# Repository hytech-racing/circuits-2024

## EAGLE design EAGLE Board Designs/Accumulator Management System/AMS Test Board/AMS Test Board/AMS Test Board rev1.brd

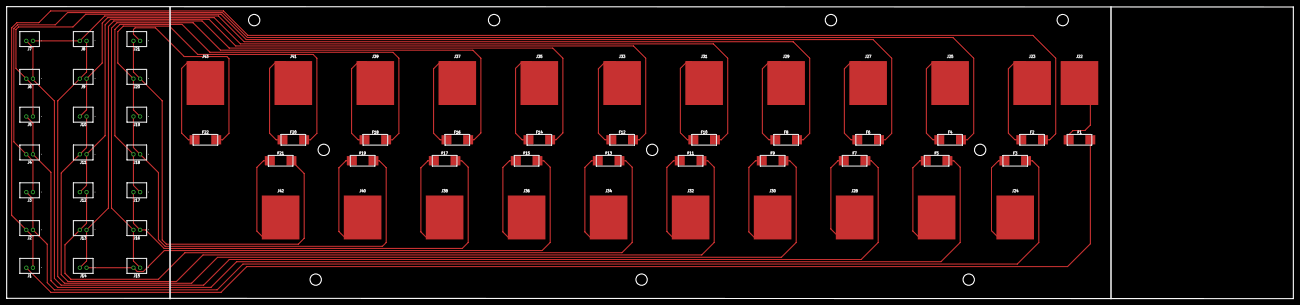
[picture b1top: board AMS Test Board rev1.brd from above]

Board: 2 copper layers, 386.6 x 87.7 mm, 75 parts (0 on the bottom side), 44 nets.

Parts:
F1, F2, F3, F4, F5, F6, F7, F8, F9, F10, F11, F12, F13, F14, F15, F16, F17, F18, F19, F20, F21, F22: FUSE_OMF_125_.5A; OMF_125
J1, J2, J3, J4, J5, J6, J7, J8, J9, J10, J11, J12, J13, J14, J15, J16, J17, J18, J19, J20, J21: CONNECTOR-2__B2B-PH-K; B2B-PH-K
J22, J23, J24, J25, J26, J27, J28, J29, J30, J31, J32, J33, J34, J35, J36, J37, J38, J39, J40, J41, J42, J43: CONNECTOR-1_5222; 5222
U$1, U$2, U$3, U$4, U$20, U$21, U$22, U$29, U$30, U$31: MOUNTING_M3

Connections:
1-: F1.2, J1.2
2-: F2.2, J1.1, J2.2
3-: F3.2, J2.1, J3.2
4-: F4.2, J3.1, J4.2
5-: F5.2, J4.1, J5.2
6-: F6.2, J5.1, J6.2
7-: F7.2, J6.1, J7.2
8-: F8.2, J7.1, J8.2
9-: F9.2, J8.1, J9.2
10-: F10.2, J9.1, J10.2
11-: F11.2, J10.1, J11.2
12-: F12.2, J11.1, J12.2
13-: F13.2, J12.1, J13.2
14-: F14.2, J13.1, J14.2
15-: F15.2, J14.1, J15.2
16-: F16.2, J15.1, J16.2
17-: F17.2, J16.1, J17.2
18-: F18.2, J17.1, J18.2
19-: F19.2, J18.1, J19.2
20-: F20.2, J19.1, J20.2
21+: F22.2, J21.1
21-: F21.2, J20.1, J21.2
unnamed: F1.1, J22.1
unnamed: F2.1, J23.1
unnamed: F3.1, J24.1
unnamed: F4.1, J25.1
unnamed: F5.1, J26.1
unnamed: F6.1, J27.1
unnamed: F7.1, J28.1
unnamed: F8.1, J29.1
unnamed: F9.1, J30.1
unnamed: F10.1, J31.1
unnamed: F11.1, J32.1
unnamed: F12.1, J33.1
unnamed: F13.1, J34.1
unnamed: F14.1, J35.1
unnamed: F15.1, J36.1
unnamed: F16.1, J37.1
unnamed: F17.1, J38.1
unnamed: F18.1, J39.1
unnamed: F19.1, J40.1
unnamed: F20.1, J41.1
unnamed: F21.1, J42.1
unnamed: F22.1, J43.1

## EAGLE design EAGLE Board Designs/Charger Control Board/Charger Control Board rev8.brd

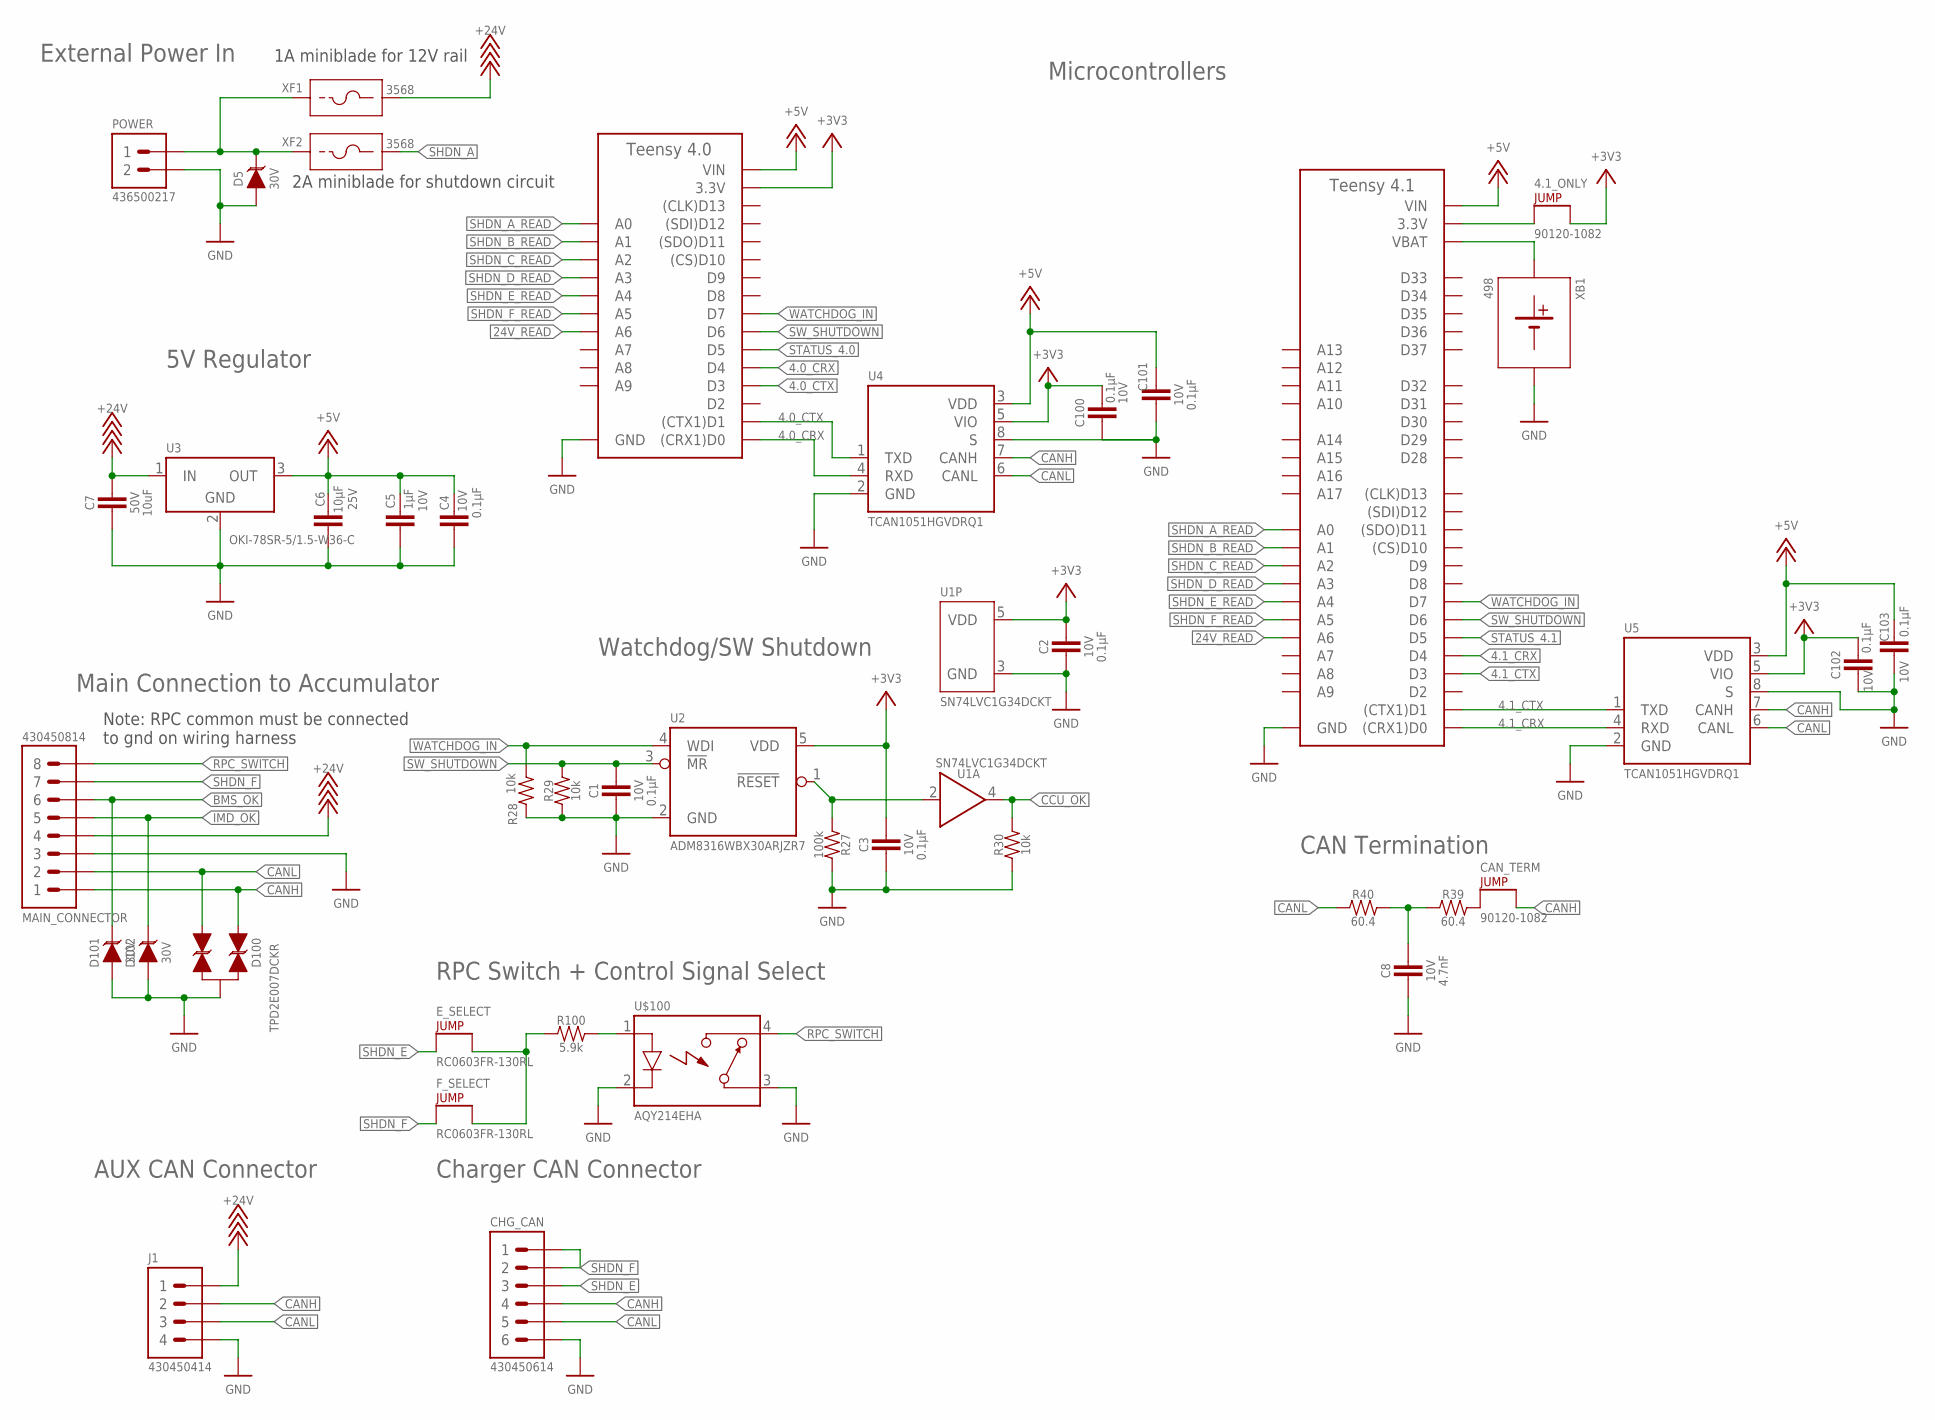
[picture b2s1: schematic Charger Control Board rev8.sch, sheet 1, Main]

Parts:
4.1_ONLY: JUMPER__1X02; 1X02
A1: TEENSY_4.1; TEENSY_LONG_EXT
A2: TEENSY_4.0TH; TEENSY_SHORT
C1, C2, C3, C4, C100, C101, C102, C103: CAPACITOR_0603_10V_0.1UF; 0603-CAP
C5: CAPACITOR_0603_10V_1UF; 0603-CAP
C6: CAPACITOR_0603_25V_10UF; 0603-CAP
C7: CAPACITOR_0805_50V_10UF; 0805-CAP
C8: CAPACITOR_0603_10V_4.7NF; 0603-CAP
CAN_TERM: JUMPER__1X02; 1X02
CHG_CAN: CONNECTOR-6_MF_T_V_; MOLEX_MICROFIT_PTH_VERTICAL_06_DUAL
D5, D101, D102: TVS_DO-214AA_30V; DO-214AA
D100: TVS_BIDIRECTIONAL_DUAL; SC-70-3
E_SELECT: JUMPER_0603_; 0603-RES
F_SELECT: JUMPER_0603_; 0603-RES
J1: CONNECTOR-4_μF_T_V_BLACK; MOLEX_MICROFIT_PTH_VERTICAL_04_DUAL
MAIN_CONNECTOR: CONNECTOR-8_MF_T_V_; MOLEX_MICROFIT_PTH_VERTICAL_08_DUAL
POWER: CONNECTOR-2_μF_T_V_; MOLEX_MICROFIT_PTH_VERTICAL_02_DUAL
R27: RESISTOR_0603_100K; 0603-RES
R28, R29, R30: RESISTOR_0603_10K; 0603-RES
R39, R40: RESISTOR_0603_60.4; 0603-RES
R100: RESISTOR_0603_5.9K; 0603-RES
U1: LOGICGATE_BUFFER; SC-70-5
U2: ADM8316WBX30; SOT-23-5
U3: VOLTAGE_REGULATOR_MODULE_OKI-78SR_5V; OKI-78SR
U4, U5: TCAN1051HQV-Q1; SOIC-08(NARROW,0.15")
U$100: RELAY_SOLIDSTATE_NO_DIP-4; DIP-4
XB1: BATTERY_HOLDER_KEYSTONE_498; 498
XF1, XF2: FUSE_HOLDER_MINIBLADEPTH; 3568

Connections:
4.0_CRX: A2.D0 ((CRX1)D0), A2.D4, U4.4 (RXD)
4.0_CTX: A2.D1 ((CTX1)D1), A2.D3, U4.1 (TXD)
4.1_CRX: A1.D0 ((CRX1)D0), A1.D4, U5.4 (RXD)
4.1_CTX: A1.D1 ((CTX1)D1), A1.D3, U5.1 (TXD)
24V_READ: A1.D20 (A6), A2.D20 (A6); also elsewhere on the board
+3V3: 4.1_ONLY.2, A2.3.3V, C2.2, C3.2, C100.2, C102.2, U1.5 (VDD), U2.5 (VDD), U4.5 (VIO), U5.5 (VIO); also elsewhere on the board
+5V: A1.VIN, A2.VIN, C4.2, C5.1, C6.1, C101.2, C103.2, U3.3 (OUT), U4.3 (VDD), U5.3 (VDD); also elsewhere on the board
+24V: C7.1, J1.1, MAIN_CONNECTOR.4, U3.1 (IN), XF1.3 (2), XF1.4 (2); also elsewhere on the board
BMS_OK: D101.2 (C), MAIN_CONNECTOR.6; also elsewhere on the board
CANH: CAN_TERM.2, CHG_CAN.4, D100.1 (C1), J1.2, MAIN_CONNECTOR.1, U4.7 (CANH), U5.7 (CANH)
CANL: CHG_CAN.5, D100.2 (C2), J1.3, MAIN_CONNECTOR.2, R40.1, U4.6 (CANL), U5.6 (CANL)
CCU_OK: R30.2, U1.4 (OUT); also elsewhere on the board
GND: A1.AGND/GND (GND), A1.GND, A1.GND@2 (GND), A2.AGND/GND (GND), A2.GND, C1.1, C2.1, C3.1, C4.1, C5.2, C6.2, C7.2, C8.2, C100.1, C101.1, C102.1, C103.1, CHG_CAN.6, D5.1 (A), D100.3 (A), D101.1 (A), D102.1 (A), J1.4, MAIN_CONNECTOR.3, POWER.2, R27.2, R28.2, R29.1, R30.1, U1.3 (GND), U2.2 (GND), U3.2 (GND), U4.2 (GND), U4.8 (S), U5.2 (GND), U5.8 (S), U$100.2 (CONTROL-), U$100.3 (CONTACT1), XB1.2 (MINUS); also elsewhere on the board
IMD_OK: D102.2 (C), MAIN_CONNECTOR.5; also elsewhere on the board
unnamed: D5.2 (C), POWER.1, XF1.1, XF1.2 (1), XF2.1, XF2.2 (1)
unnamed: R27.1, U1.2 (IN), U2.1 (!RESET!)
unnamed: CAN_TERM.1, R39.2
unnamed: E_SELECT.2, F_SELECT.2, R100.1
unnamed: A1.VBAT, XB1.1 (PLUS)
unnamed: C8.1, R39.1, R40.2
unnamed: R100.2, U$100.1 (CONTROL+)
unnamed: 4.1_ONLY.1, A1.3V3 (3.3V), A1.3V3@2 (3.3V), A1.3V3@3 (3.3V)
RPC_SWITCH: MAIN_CONNECTOR.8, U$100.4 (CONTACT2)
SHDN_A: XF2.3 (2), XF2.4 (2); also elsewhere on the board
SHDN_A_READ: A1.D14 (A0), A2.D14 (A0); also elsewhere on the board
SHDN_B_READ: A1.D15 (A1), A2.D15 (A1); also elsewhere on the board
SHDN_C_READ: A1.D16 (A2), A2.D16 (A2); also elsewhere on the board
SHDN_D_READ: A1.D17 (A3), A2.D17 (A3); also elsewhere on the board
SHDN_E: CHG_CAN.3, E_SELECT.1; also elsewhere on the board
SHDN_E_READ: A1.D18 (A4), A2.D18 (A4); also elsewhere on the board
SHDN_F: CHG_CAN.1, CHG_CAN.2, F_SELECT.1, MAIN_CONNECTOR.7; also elsewhere on the board
SHDN_F_READ: A1.D19 (A5), A2.D19 (A5); also elsewhere on the board
STATUS_4.0: A2.D5; also elsewhere on the board
STATUS_4.1: A1.D5; also elsewhere on the board
SW_SHUTDOWN: A1.D6, A2.D6, C1.2, R29.2, U2.3 (!MR!)
WATCHDOG_IN: A1.D7, A2.D7, R28.1, U2.4 (WDI)

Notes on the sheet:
External Power In
5V Regulator
Main Connection to Accumulator
CAN Termination
Microcontrollers
Watchdog/SW Shutdown
Charger CAN Connector
AUX CAN Connector
1A miniblade for 12V rail
2A miniblade for shutdown circuit
RPC Switch + Control Signal Select
Note: RPC common must be connected to gnd on wiring harness

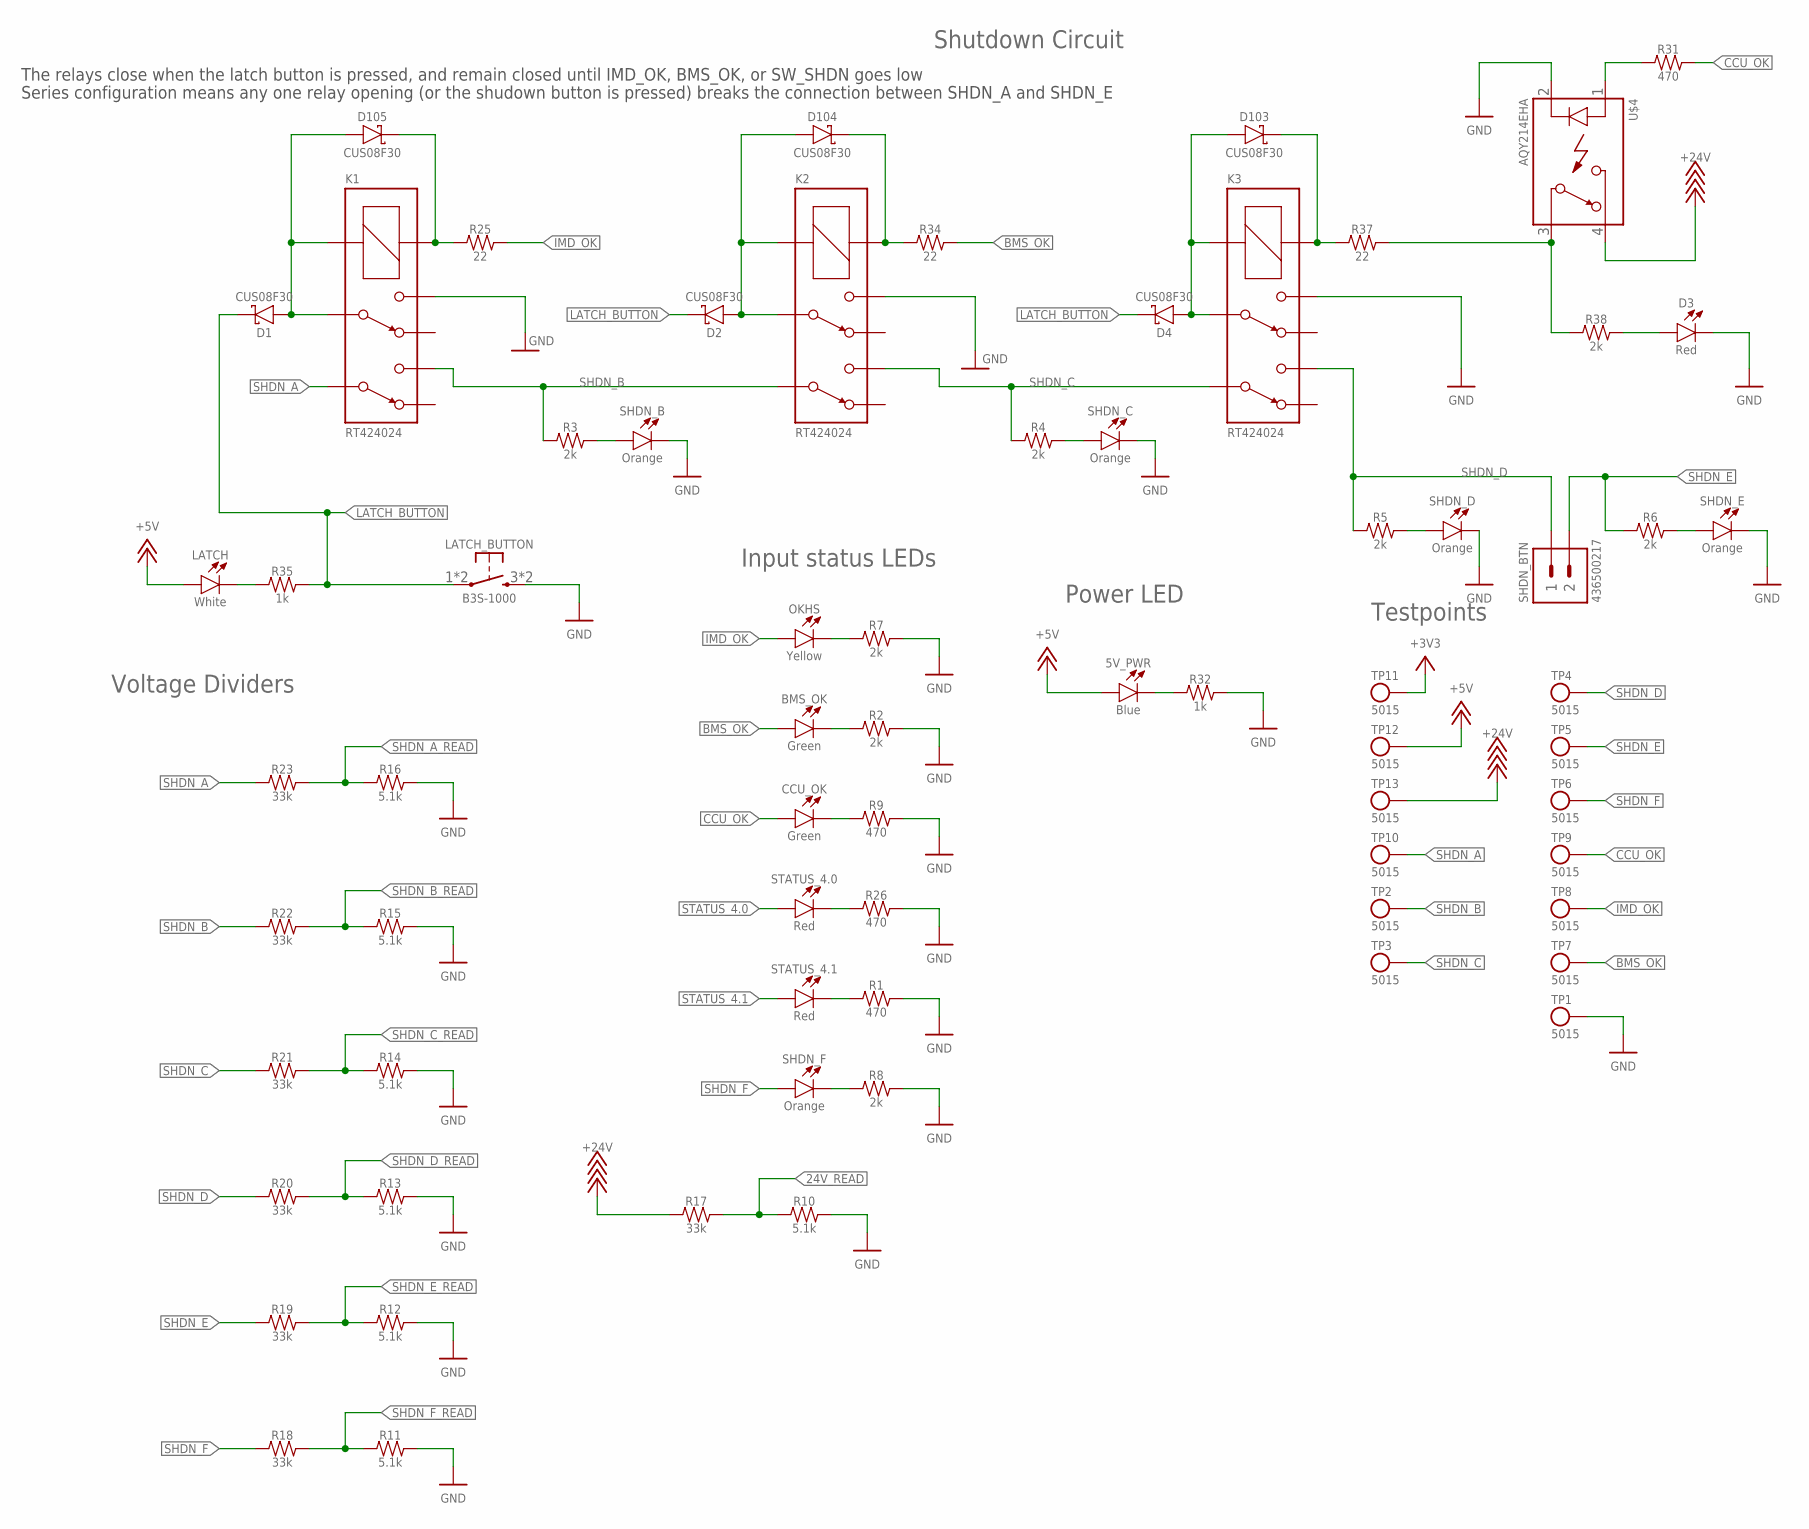
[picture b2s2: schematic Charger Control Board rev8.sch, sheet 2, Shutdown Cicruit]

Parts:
5V_PWR: LED_0603_BLUE; 0603-LED
BMS_OK: LED_0603_GREEN; 0603-LED
CCU_OK: LED_0603_GREEN; 0603-LED
D1, D2, D4, D103, D104, D105: SCHOTTKY_SOD323_30V; SOD-323
D3: LED_0603_RED; 0603-LED
K1, K2, K3: RELAY_DPDT_RT424024TH; RT*2*
LATCH: LED_0603_WHITE; 0603-LED
LATCH_BUTTON: BUTTON; B3S-100X
OKHS: LED_0603_YELLOW; 0603-LED
R1, R9, R26, R31: RESISTOR_0603_470; 0603-RES
R2, R3, R4, R5, R6, R7, R8, R38: RESISTOR_0603_2K; 0603-RES
R10, R11, R12, R13, R14, R15, R16: RESISTOR_0603_5.1K; 0603-RES
R17, R18, R19, R20, R21, R22, R23: RESISTOR_0603_33K; 0603-RES
R25, R34, R37: RESISTOR_0603_22; 0603-RES
R32, R35: RESISTOR_0603_1K; 0603-RES
SHDN_B: LED_0603_ORANGE; 0603-LED
SHDN_BTN: CONNECTOR-2_μF_T_V_; MOLEX_MICROFIT_PTH_VERTICAL_02_DUAL
SHDN_C: LED_0603_ORANGE; 0603-LED
SHDN_D: LED_0603_ORANGE; 0603-LED
SHDN_E: LED_0603_ORANGE; 0603-LED
SHDN_F: LED_0603_ORANGE; 0603-LED
STATUS_4.0, STATUS_4.1: LED_0603_RED; 0603-LED
TP1, TP2, TP3, TP4, TP5, TP6, TP7, TP8, TP9, TP10, TP11, TP12, TP13: TEST_POINT; 5015
U$4: RELAY_SOLIDSTATE_NO; DIP-4@1

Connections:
24V_READ: R10.1, R17.2; also elsewhere on the board
+3V3: TP11.1; also elsewhere on the board
+5V: 5V_PWR.2 (A), LATCH.2 (A), TP12.1; also elsewhere on the board
+24V: R17.1, TP13.1, U$4.4 (CONTACT2); also elsewhere on the board
BMS_OK: BMS_OK.2 (A), R34.2, TP7.1; also elsewhere on the board
CCU_OK: CCU_OK.2 (A), R31.2, TP9.1; also elsewhere on the board
GND: D3.1 (C), K1.14 (4), K2.14 (4), K3.14 (4), LATCH_BUTTON.3 (S), LATCH_BUTTON.4 (S), R1.2, R2.2, R7.2, R8.2, R9.2, R10.2, R11.2, R12.2, R13.2, R14.2, R15.2, R16.2, R26.2, R32.2, SHDN_B.1 (C), SHDN_C.1 (C), SHDN_D.1 (C), SHDN_E.1 (C), TP1.1, U$4.2 (CONTROL-); also elsewhere on the board
IMD_OK: OKHS.2 (A), R25.2, TP8.1; also elsewhere on the board
LATCH_BUTTON: D1.C, D2.C, D4.C, LATCH_BUTTON.1, LATCH_BUTTON.2, R35.2
unnamed: R8.1, SHDN_F.1 (C)
unnamed: R31.1, U$4.1 (CONTROL+)
unnamed: D1.A, D105.A, K1.11 (3), K1.A2 (COIL-)
unnamed: D105.C, K1.A1 (COIL+), R25.1
unnamed: D104.C, K2.A1 (COIL+), R34.1
unnamed: D2.A, D104.A, K2.11 (3), K2.A2 (COIL-)
unnamed: D103.C, K3.A1 (COIL+), R37.1
unnamed: R37.2, R38.1, U$4.3 (CONTACT1)
unnamed: LATCH.1 (C), R35.1
unnamed: R5.2, SHDN_D.2 (A)
unnamed: R6.2, SHDN_E.2 (A)
unnamed: D4.A, D103.A, K3.11 (3), K3.A2 (COIL-)
unnamed: D3.2 (A), R38.2
unnamed: R4.2, SHDN_C.2 (A)
unnamed: R3.2, SHDN_B.2 (A)
unnamed: OKHS.1 (C), R7.1
unnamed: BMS_OK.1 (C), R2.1
unnamed: CCU_OK.1 (C), R9.1
unnamed: R26.1, STATUS_4.0.1 (C)
unnamed: 5V_PWR.1 (C), R32.1
unnamed: R1.1, STATUS_4.1.1 (C)
SHDN_A: K1.21 (6), R23.1, TP10.1; also elsewhere on the board
SHDN_A_READ: R16.1, R23.2; also elsewhere on the board
SHDN_B: K1.24 (5), K2.21 (6), R3.1, R22.1, TP2.1
SHDN_B_READ: R15.1, R22.2; also elsewhere on the board
SHDN_C: K2.24 (5), K3.21 (6), R4.1, R21.1, TP3.1
SHDN_C_READ: R14.1, R21.2; also elsewhere on the board
SHDN_D: K3.24 (5), R5.1, R20.1, SHDN_BTN.1, TP4.1
SHDN_D_READ: R13.1, R20.2; also elsewhere on the board
SHDN_E: R6.1, R19.1, SHDN_BTN.2, TP5.1; also elsewhere on the board
SHDN_E_READ: R12.1, R19.2; also elsewhere on the board
SHDN_F: R18.1, SHDN_F.2 (A), TP6.1; also elsewhere on the board
SHDN_F_READ: R11.1, R18.2; also elsewhere on the board
STATUS_4.0: STATUS_4.0.2 (A); also elsewhere on the board
STATUS_4.1: STATUS_4.1.2 (A); also elsewhere on the board

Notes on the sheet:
Input status LEDs
Power LED
Voltage Dividers
Shutdown Circuit
Testpoints
The relays close when the latch button is pressed, and remain closed until IMD_OK, BMS_OK, or SW_SHDN goes low
Series configuration means any one relay opening (or the shudown button is pressed) breaks the connection between SHDN_A and SHDN_E

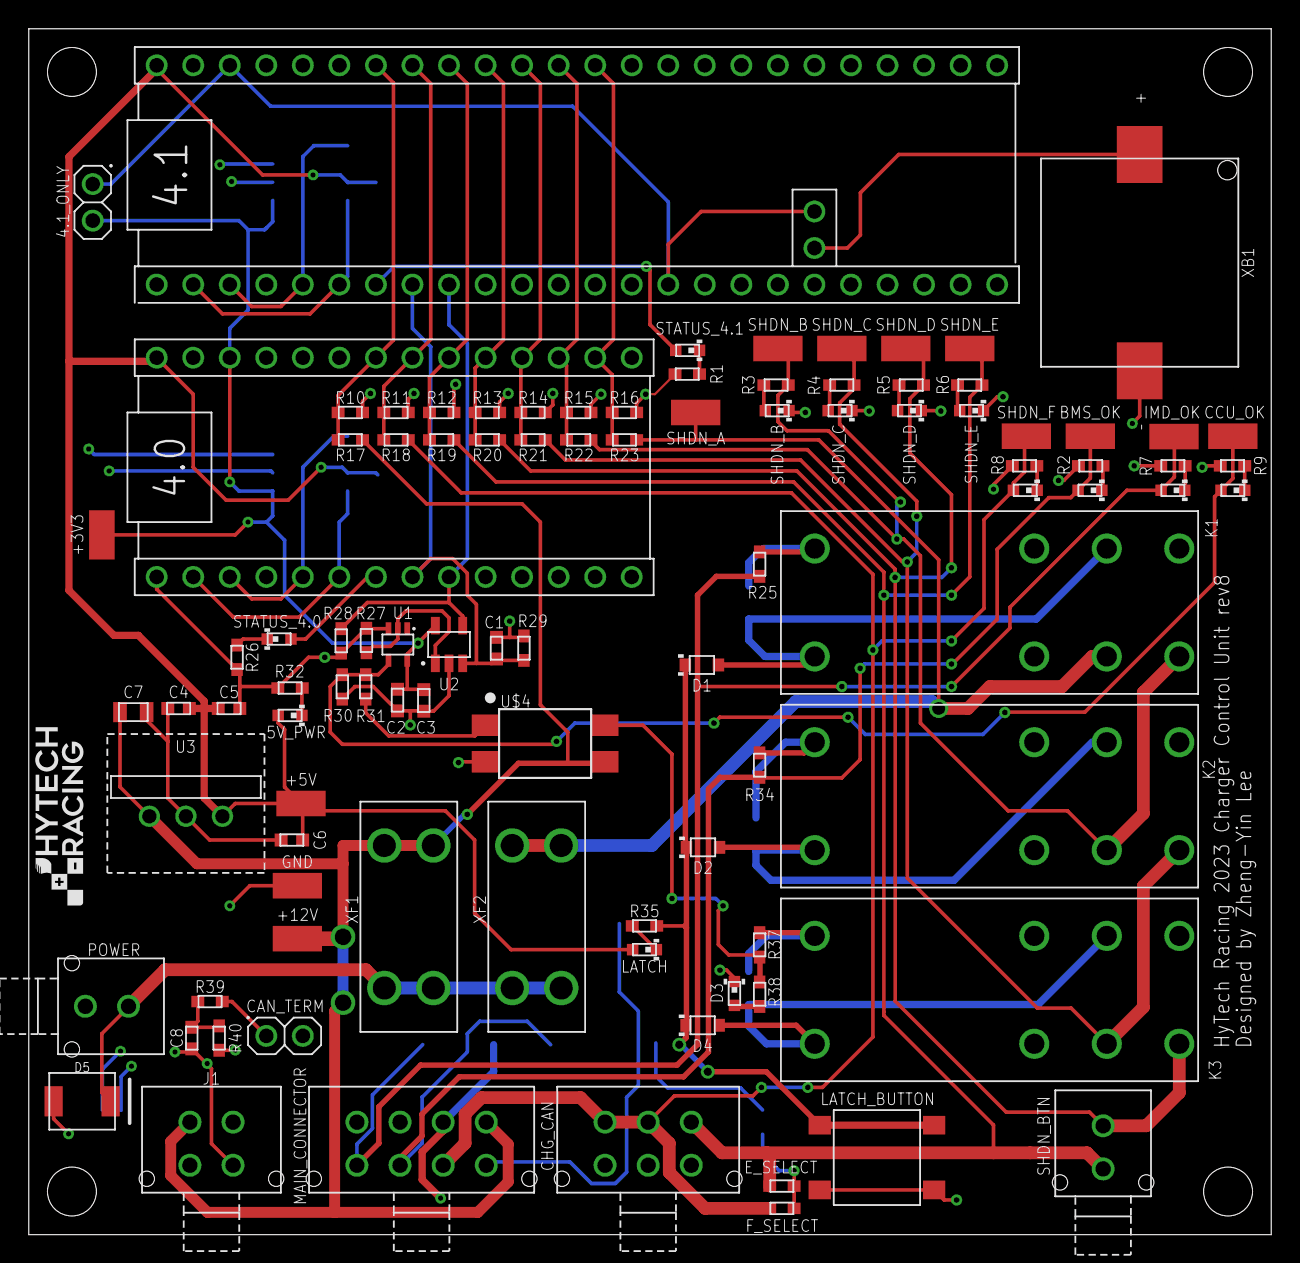
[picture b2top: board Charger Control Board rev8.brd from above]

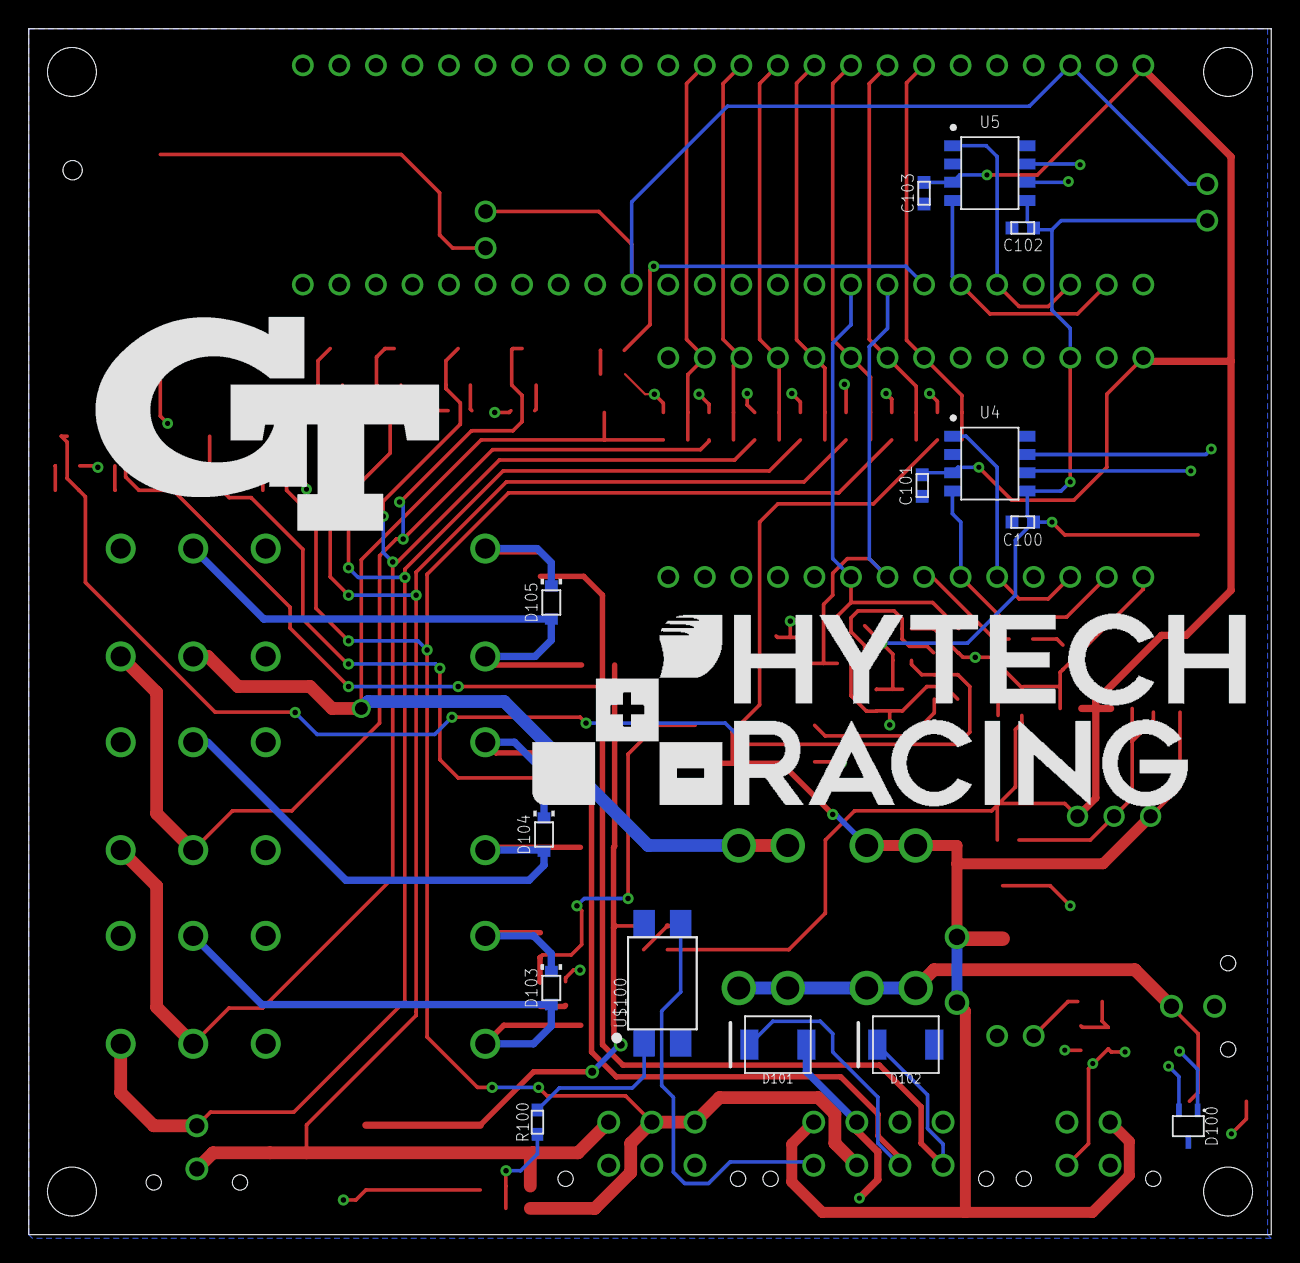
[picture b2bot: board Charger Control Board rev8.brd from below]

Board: 4 copper layers, 86.4 x 83.8 mm, 118 parts (16 on the bottom side), 61 nets.

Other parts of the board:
U$1, U$2, U$6, U$7: MOUNTING_M3
U$3: LOGO_HYTECH_SMALL
U$9: LOGO_HYTECH_LARGE
U$10: LOGO_GT_LARGE

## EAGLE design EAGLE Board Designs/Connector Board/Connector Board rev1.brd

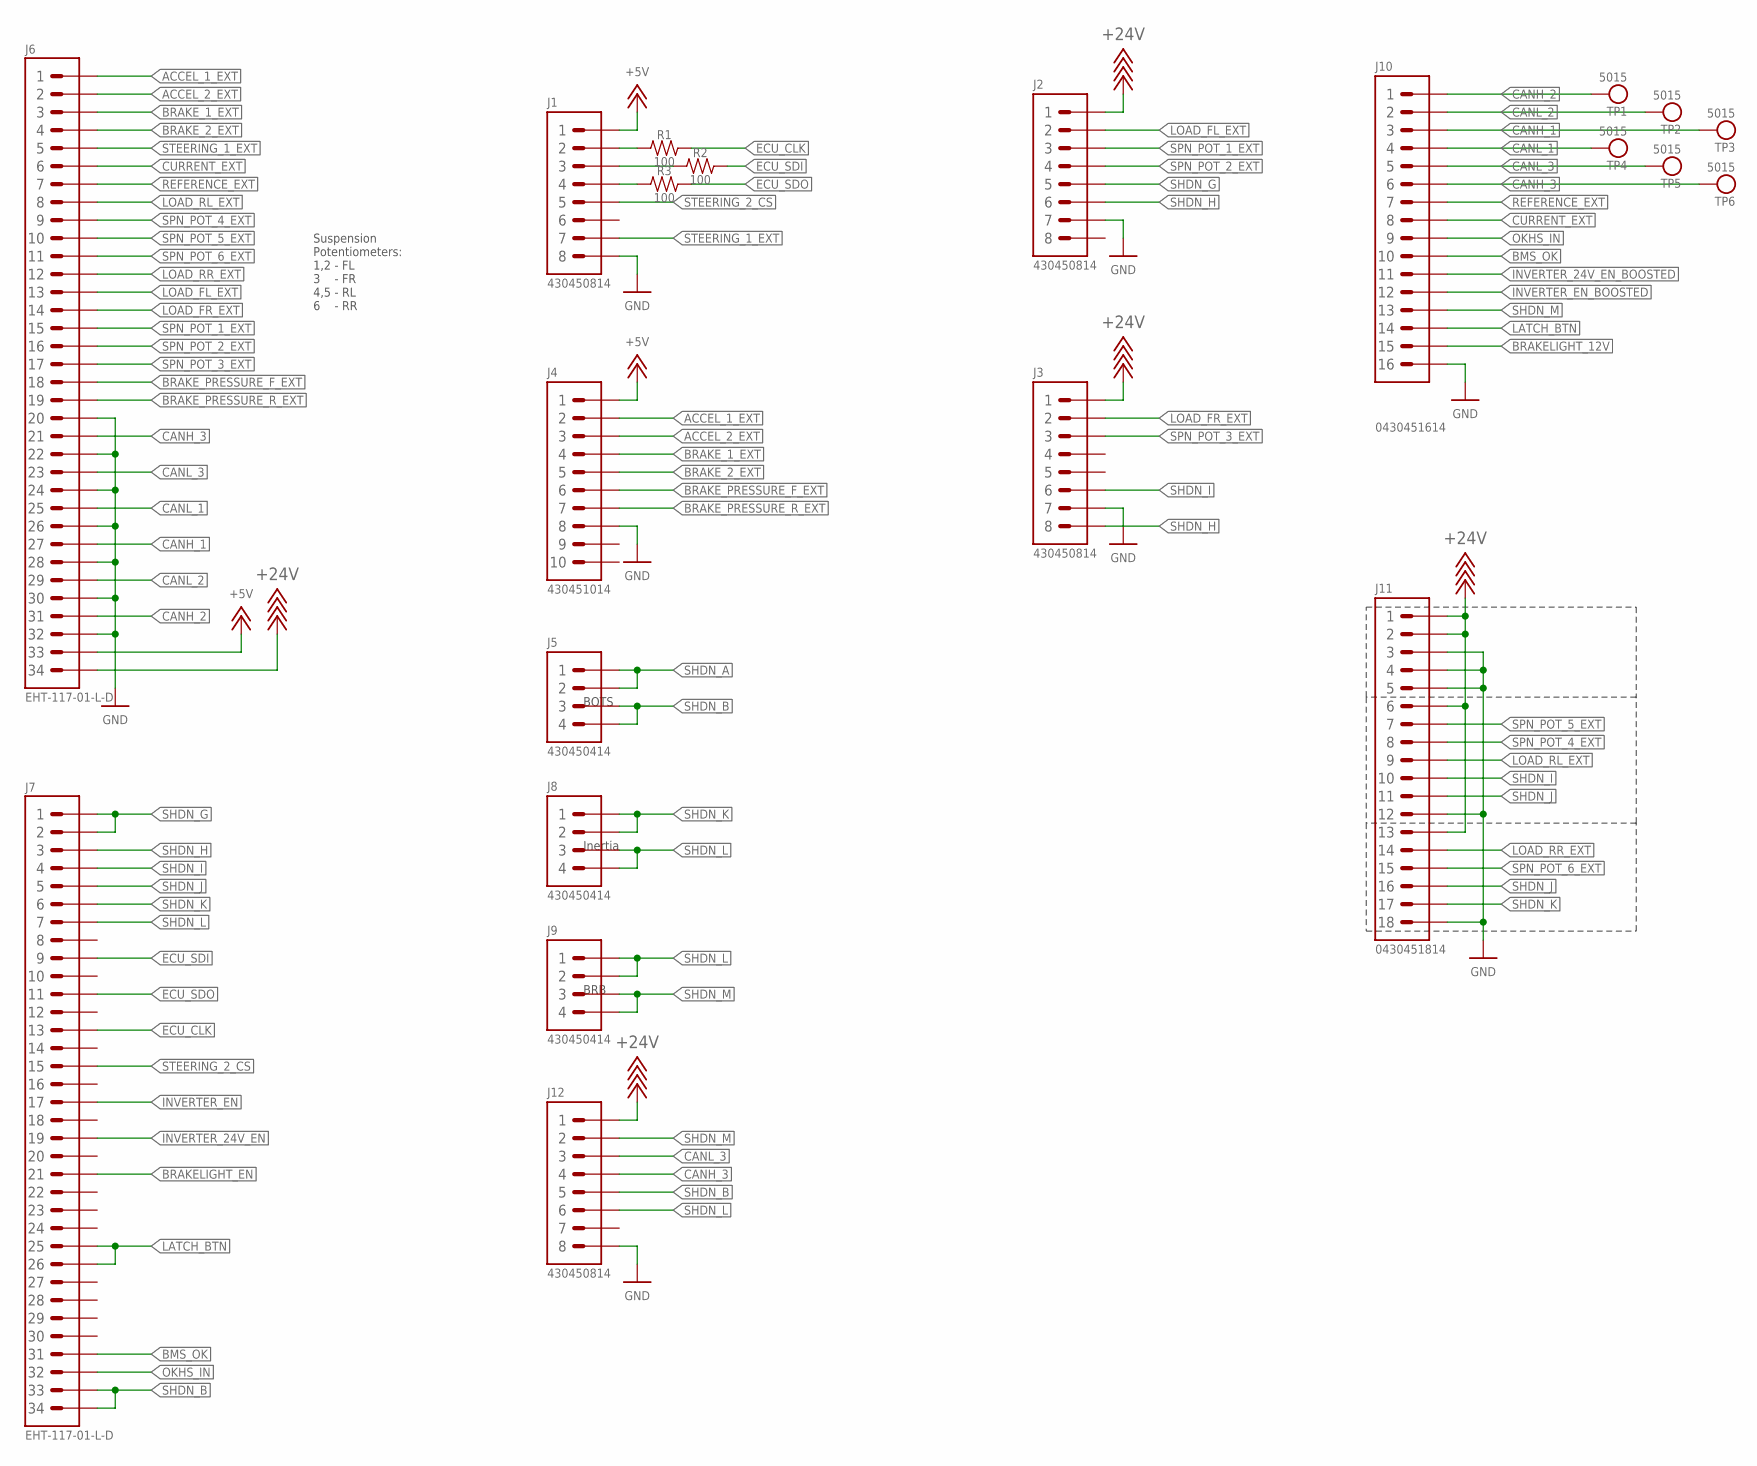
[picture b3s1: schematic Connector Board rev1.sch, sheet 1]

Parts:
J1, J2, J3, J12: CONNECTOR-8_μF_T_V_BLACK; MOLEX_MICROFIT_PTH_VERTICAL_08_DUAL
J4: CONNECTOR-10_MF_T_V_; MOLEX_MICROFIT_PTH_VERTICAL_10_DUAL
J5, J8, J9: CONNECTOR-4_μF_T_V_BLACK; MOLEX_MICROFIT_PTH_VERTICAL_04_DUAL
J6, J7: CONNECTOR-34__; EHT-117-01
J10: CONNECTOR-16_MF_T_V_; MOLEX_MICROFIT_PTH_VERTICAL_16_DUAL
J11: CONNECTOR-18_MF_T_V_; MOLEX_MICROFIT_PTH_VERTICAL_18_DUAL
R1, R2, R3: RESISTOR_0603_100; 0603-RES
TP1, TP2, TP3, TP4, TP5, TP6: TEST_POINT; 5015

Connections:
!STEERING_2_CS: J1.5, J7.15
+5V: J1.1, J4.1, J6.33
+24V: J2.1, J3.1, J6.34, J11.1, J11.2, J11.6, J11.13, J12.1; also elsewhere on the board
ACCEL_1_EXT: J4.2, J6.1
ACCEL_2_EXT: J4.3, J6.2
BMS_OK: J7.31, J10.10
BRAKELIGHT_12V: J10.15; also elsewhere on the board
BRAKELIGHT_EN: J7.21; also elsewhere on the board
BRAKE_1_EXT: J4.4, J6.3
BRAKE_2_EXT: J4.5, J6.4
BRAKE_PRESSURE_F_EXT: J4.6, J6.18; also elsewhere on the board
BRAKE_PRESSURE_R_EXT: J4.7, J6.19; also elsewhere on the board
CANH_1: J6.27, J10.3, TP3.1
CANH_2: J6.31, J10.1, TP1.1
CANH_3: J6.21, J10.6, J12.4, TP6.1
CANL_1: J6.25, J10.4, TP4.1
CANL_2: J6.29, J10.2, TP2.1
CANL_3: J6.23, J10.5, J12.3, TP5.1
CURRENT_EXT: J6.6, J10.8
ECU_CLK: J7.13, R1.2
ECU_SDI: J7.9, R2.2
ECU_SDO: J7.11, R3.2
GND: J1.8, J2.7, J3.7, J4.8, J6.20, J6.22, J6.24, J6.26, J6.28, J6.30, J6.32, J10.16, J11.3, J11.4, J11.5, J11.12, J11.18, J12.8; also elsewhere on the board
INVERTER_24V_EN: J7.19; also elsewhere on the board
INVERTER_24V_EN_BOOSTED: J10.11; also elsewhere on the board
INVERTER_EN: J7.17; also elsewhere on the board
INVERTER_EN_BOOSTED: J10.12; also elsewhere on the board
LATCH_BTN: J7.25, J7.26, J10.14
LOAD_FL_EXT: J2.2, J6.13
LOAD_FR_EXT: J3.2, J6.14
LOAD_RL_EXT: J6.8, J11.9
LOAD_RR_EXT: J6.12, J11.14
unnamed: J1.2, R1.1
unnamed: J1.3, R2.1
unnamed: J1.4, R3.1
OKHS_IN: J7.32, J10.9
REFERENCE_EXT: J6.7, J10.7
SHDN_A: J5.1, J5.2; also elsewhere on the board
SHDN_B: J5.3, J5.4, J7.33, J7.34, J12.5
SHDN_G: J2.5, J7.1, J7.2
SHDN_H: J2.6, J3.8, J7.3
SHDN_I: J3.6, J7.4, J11.10
SHDN_J: J7.5, J11.11, J11.16
SHDN_K: J7.6, J8.1, J8.2, J11.17
SHDN_L: J7.7, J8.3, J8.4, J9.1, J9.2, J12.6
SHDN_M: J9.3, J9.4, J10.13, J12.2
SPN_POT_1_EXT: J2.3, J6.15
SPN_POT_2_EXT: J2.4, J6.16
SPN_POT_3_EXT: J3.3, J6.17
SPN_POT_4_EXT: J6.9, J11.8
SPN_POT_5_EXT: J6.10, J11.7
SPN_POT_6_EXT: J6.11, J11.15
STEERING_1_EXT: J1.7, J6.5

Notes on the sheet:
Suspension Potentiometers: 1,2 - FL 3 - FR 4,5 - RL 6 - RR
BOTS
Inertia
BRB

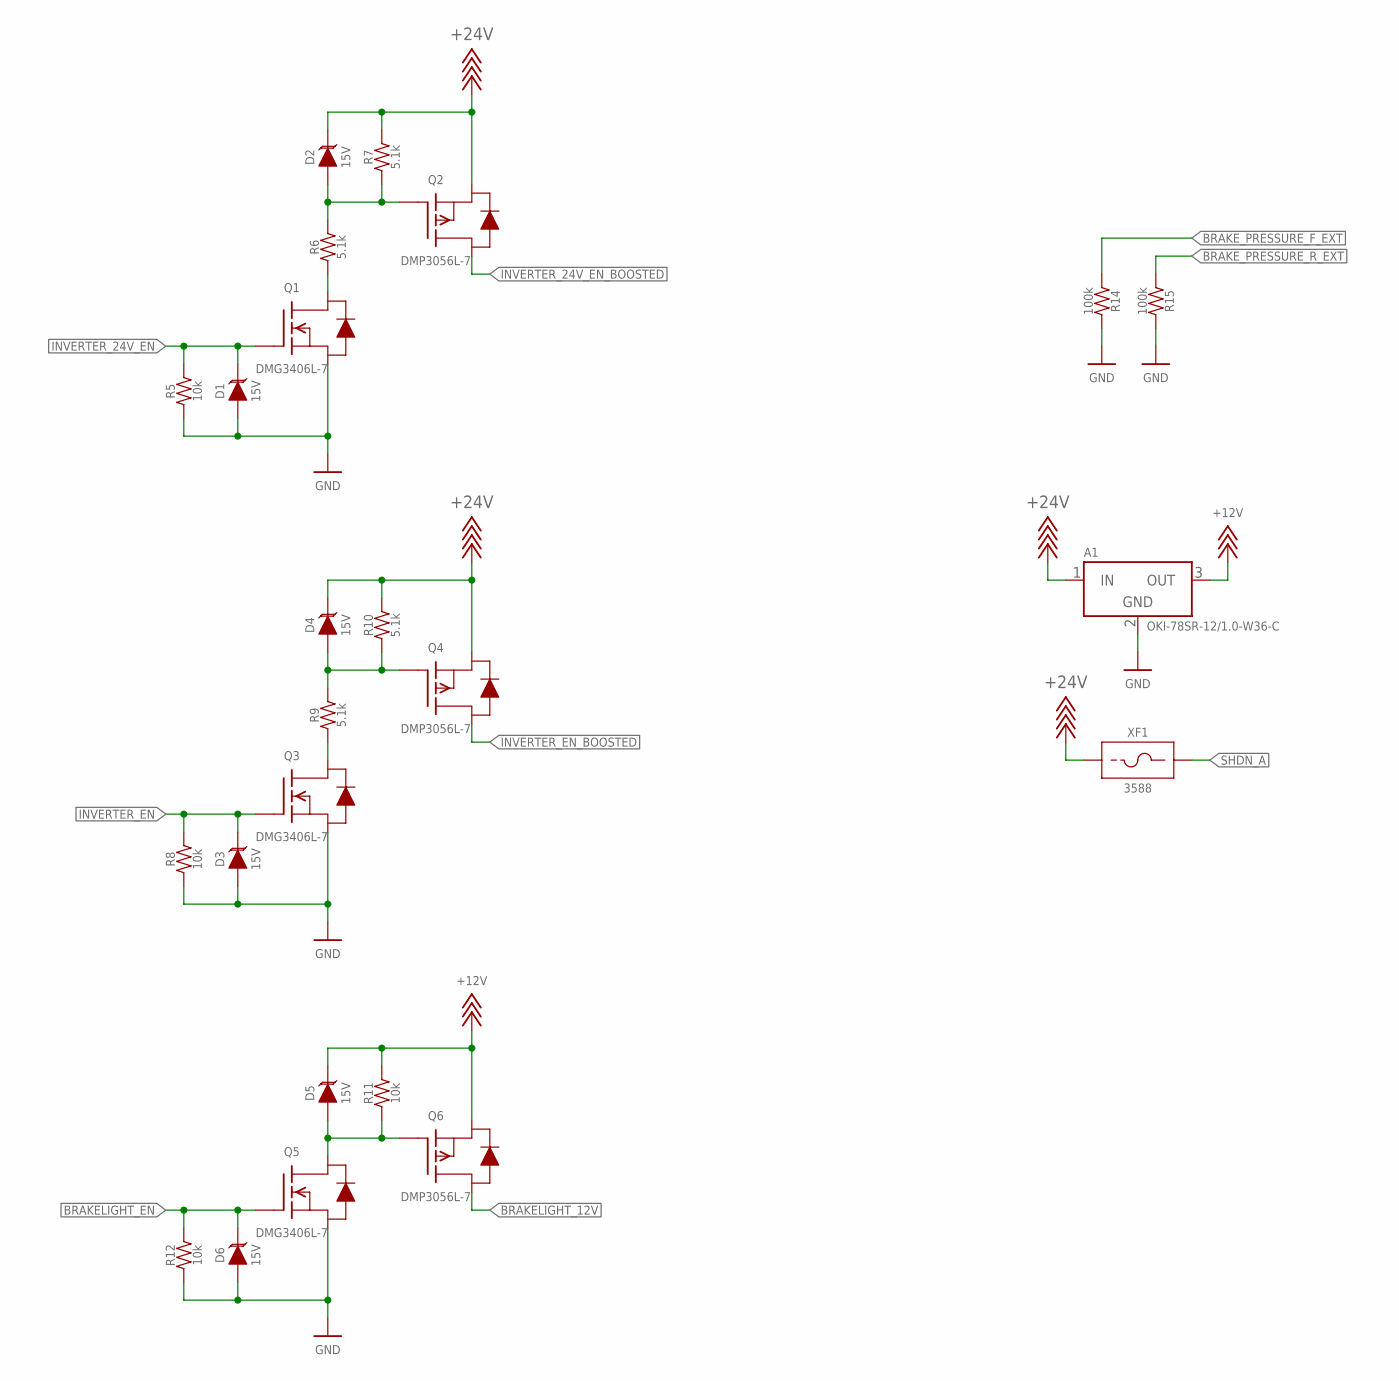
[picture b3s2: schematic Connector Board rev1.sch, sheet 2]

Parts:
A1: VOLTAGE_REGULATOR_MODULE_OKI-78SR_12V; OKI-78SR
D1, D2, D3, D4, D5, D6: TVS__15V; SOT-23
Q1, Q3, Q5: TRANSISTOR_N_MOS__DMG3406L-7; SOT-23
Q2, Q4, Q6: TRANSISTOR_P_MOS_SOT-23_DMP3056L-7; SOT-23
R5, R8, R11, R12: RESISTOR_0603_10K; 0603-RES
R6, R7, R9, R10: RESISTOR_0603_5.1K; 0603-RES
R14, R15: RESISTOR_0603_100K; 0603-RES
XF1: FUSE_HOLDER_MINIBLADESMD; 3588

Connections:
+12V: A1.3 (OUT), D5.3 (C), Q6.2 (S), R11.2
+24V: A1.1 (IN), D2.3 (C), D4.3 (C), Q2.2 (S), Q4.2 (S), R7.2, R10.2, XF1.1, XF1.2 (1); also elsewhere on the board
BRAKELIGHT_12V: Q6.3 (D); also elsewhere on the board
BRAKELIGHT_EN: D6.3 (C), Q5.1 (G), R12.2; also elsewhere on the board
BRAKE_PRESSURE_F_EXT: R14.1; also elsewhere on the board
BRAKE_PRESSURE_R_EXT: R15.1; also elsewhere on the board
GND: A1.2 (GND), D1.1 (A), D3.1 (A), D6.1 (A), Q1.2 (S), Q3.2 (S), Q5.2 (S), R5.1, R8.1, R12.1, R14.2, R15.2; also elsewhere on the board
INVERTER_24V_EN: D1.3 (C), Q1.1 (G), R5.2; also elsewhere on the board
INVERTER_24V_EN_BOOSTED: Q2.3 (D); also elsewhere on the board
INVERTER_EN: D3.3 (C), Q3.1 (G), R8.2; also elsewhere on the board
INVERTER_EN_BOOSTED: Q4.3 (D); also elsewhere on the board
unnamed: D2.1 (A), Q2.1 (G), R6.2, R7.1
unnamed: Q1.3 (D), R6.1
unnamed: D4.1 (A), Q4.1 (G), R9.2, R10.1
unnamed: Q3.3 (D), R9.1
unnamed: D5.1 (A), Q5.3 (D), Q6.1 (G), R11.1
SHDN_A: XF1.3 (2), XF1.4 (2); also elsewhere on the board
